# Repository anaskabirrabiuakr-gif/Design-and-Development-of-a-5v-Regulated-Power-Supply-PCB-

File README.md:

# Design-and-Development-of-a-5v-Regulated-Power-Supply-PCB-
Designed and developed regulated power supply using LM7805 for a stable 5v output. Designed the circuit schematics and PCB layout using Kicad, selected appropriate rectification, filtering, regulation and protection components. Successfully tested and validated a stable 5v DC output for embedded applications.

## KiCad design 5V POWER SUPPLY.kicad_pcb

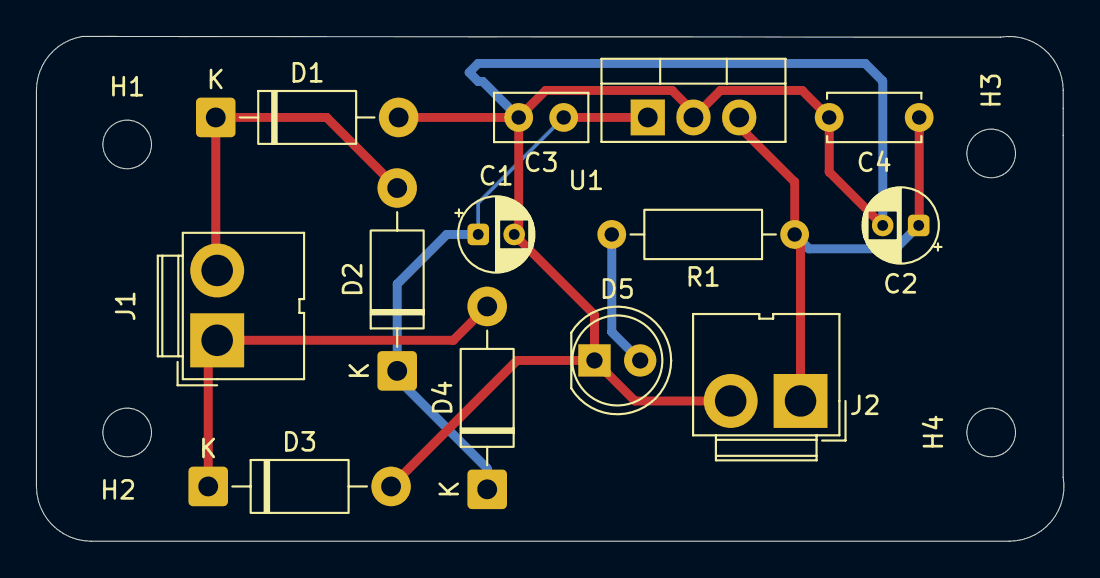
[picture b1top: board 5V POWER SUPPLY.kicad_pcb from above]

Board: 2 copper layers, 57.1 x 28.0 mm, 17 parts (0 on the bottom side), 6 nets.

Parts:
C1: 470uF; CP_Radial_D4.0mm_P2.00mm
C2: 100uF; CP_Radial_D4.0mm_P2.00mm
C3: 0.33uF; C_Disc_D5.0mm_W2.5mm_P2.50mm
C4: 0.1uF; C_Disc_D5.0mm_W2.5mm_P5.00mm
D1, D2, D3, D4: 1N4007; D_DO-41_SOD81_P10.16mm_Horizontal
D5: LED; LED_D5.0mm
H1, H2, H3, H4: MountingHole; MountingHole_2.7mm_M2.5_ISO14580
J1, J2: Screw_Terminal_01x02; JWT_A3963_1x02_P3.96mm_Vertical
R1: 330 Ohms; R_Axial_DIN0207_L6.3mm_D2.5mm_P10.16mm_Horizontal
U1: LM7805_TO220; TO-220-3_Vertical

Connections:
unnamed: C1.2, C2.2, C3.2, C4.2, D1.2 (A), D3.2 (A), D5.1 (K), J2.2, U1.2 (GND)
unnamed: D1.1 (K), D2.2 (A), J1.2
unnamed: C1.1, C3.1, D2.1 (K), D4.1 (K), U1.1 (VI)
unnamed: D3.1 (K), D4.2 (A), J1.1
unnamed: D5.2 (A), R1.2
unnamed: C2.1, C4.1, J2.1, R1.1, U1.3 (VO)
